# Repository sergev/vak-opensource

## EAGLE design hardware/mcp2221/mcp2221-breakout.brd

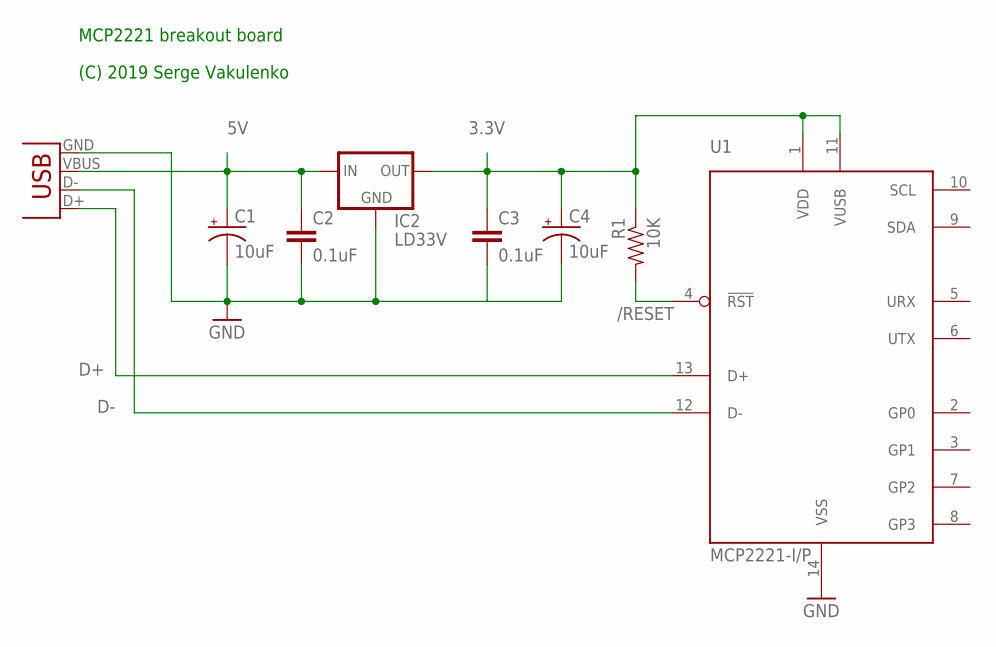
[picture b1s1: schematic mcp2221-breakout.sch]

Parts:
C1, C4: 10uF; CPOL-RADIAL-10UF-25V
C2: 0.1uF; CAP-PTH-SMALL
C3: 0.1uF; CAP-PTH-5MM
IC2: LD33V; 78XXL
R1: 10K; AXIAL-0.3
U1: MCP2221-I/P; DIL14
X1: USBPTH; USB-B-PTH

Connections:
3.3V: C3.1, C4.1 (+), IC2.OUT, R1.P$1 (1), U1.1 (VDD), U1.11 (VUSB)
5V: C1.1 (+), C2.1, IC2.IN, X1.VBUS
/RESET: R1.P$2 (2), U1.4 (!RST)
D+: U1.13 (D+), X1.D+
D-: U1.12 (D-), X1.D-
GND: C1.2 (-), C2.2, C3.2, C4.2 (-), IC2.GND, U1.14 (VSS), X1.GND

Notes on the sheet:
MCP2221 breakout board
(C) 2019 Serge Vakulenko

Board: 2 copper layers, 8 parts (0 on the bottom side), 6 nets, no tracks yet.

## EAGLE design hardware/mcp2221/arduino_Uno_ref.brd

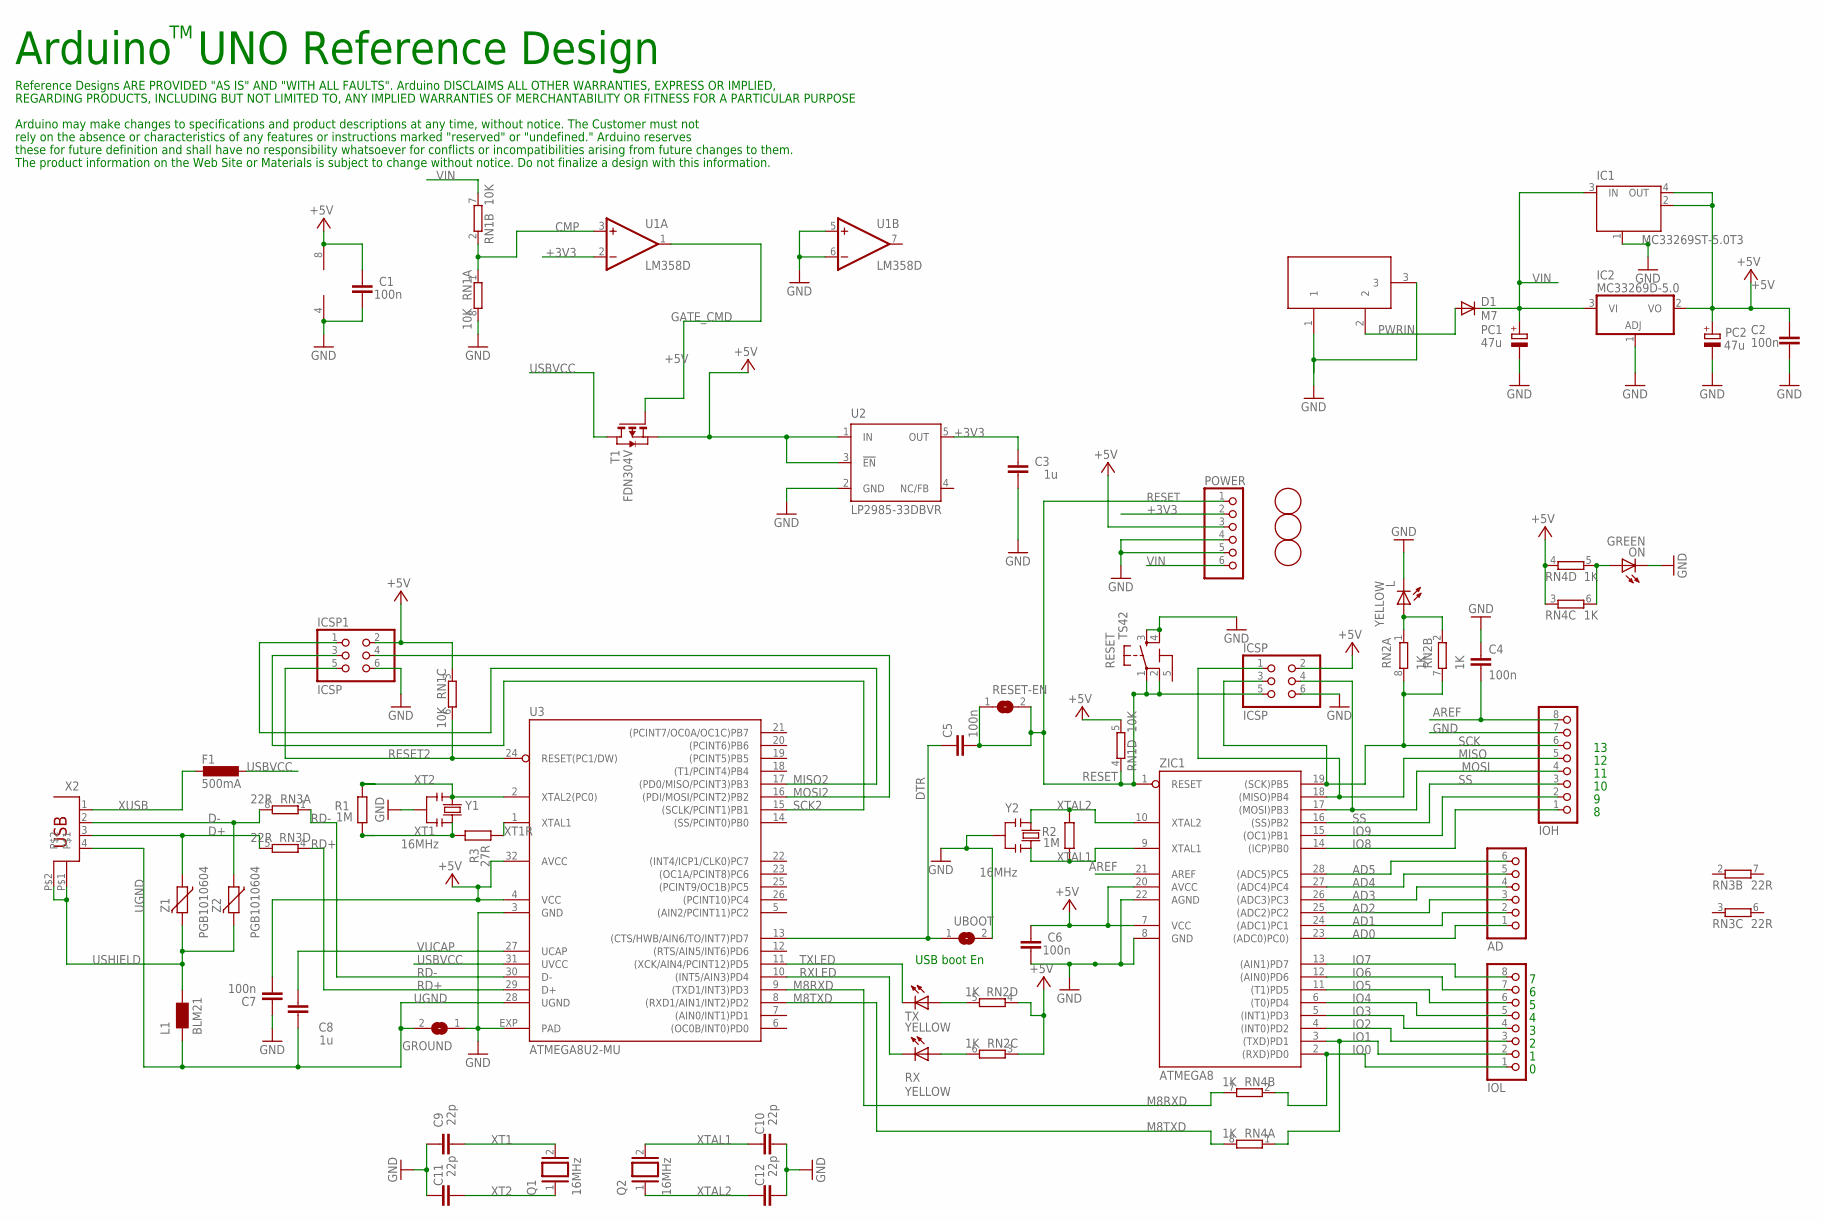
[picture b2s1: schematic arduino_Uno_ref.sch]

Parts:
AD: PINHD-1X6; 1X06
C1, C2, C4, C5, C6, C7: 100n; C0603-ROUND
C3, C8: 1u; C0603-ROUND
C9, C10, C11, C12: 22p; C0603-ROUND
D1: M7; SMB
F1: 500mA; L1812
GROUND: SJ
IC1: MC33269ST-5.0T3; SOT223
IC2: MC33269D-5.0; DPACK
ICSP, ICSP1: ICSP; 2X03
IOH: PINHD-1X8; 1X08
IOL: PINHD-1X8; 1X08
L: YELLOW; CHIP-LED0805
L1: BLM21; 0805
ON: GREEN; CHIP-LED0805
PC1, PC2: 47u; PANASONIC_D
POWER: PINHD-1X6; 1X06
Q1, Q2: 16MHz; QS
R1, R2: 1M; R0603-ROUND
R3: 27R; R0603-ROUND
RESET: TS42
RESET-EN: SJ
RN1: 10K; CAY16
RN2, RN4: 1K; CAY16
RN3: 22R; CAY16
RX: YELLOW; CHIP-LED0805
T1: FDN304V; SOT-23
TX: YELLOW; CHIP-LED0805
U1: LM358D; SO08
U2: LP2985-33DBVR; SOT23-DBV
U3: ATMEGA8U2-MU; QFN32
U$3, U$4, U$6: FIDUCIALMOUNT; FIDUCIA-MOUNT
UBOOT: SJ
X1: DC21MMX; DC-21MM
X2: PN61729
Y1, Y2: 16MHz; RESONATOR
Z1, Z2: PGB1010604; CT/CN0603
ZIC1: ATMEGA8; DIL28-3

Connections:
5-GND: RESET.5 (5-GND)
+3V3: C3.2, POWER.2, U1.2 (-IN), U2.5 (OUT)
+5V: C1.2, C2.2, C6.2, C7.1, IC1.2 (OUT), IC1.4 (OUT), IC2.2 (VO), ICSP.2, ICSP1.2, PC2.+, POWER.3, RN1.3 (1), RN1.5 (2), RN2.3 (1), RN2.4 (1), RN4.3 (1), RN4.4 (1), T1.2 (S), U1.8 (V+), U2.1 (IN), U2.3 (!EN), U3.4 (VCC), U3.32 (AVCC), ZIC1.7 (VCC), ZIC1.20 (AVCC)
AD0: AD.1, ZIC1.23 ((ADC0)PC0))
AD1: AD.2, ZIC1.24 ((ADC1)PC1)
AD2: AD.3, ZIC1.25 ((ADC2)PC2)
AD3: AD.4, ZIC1.26 ((ADC3)PC3)
AD4: AD.5, ZIC1.27 ((ADC4)PC4)
AD5: AD.6, ZIC1.28 ((ADC5)PC5)
AREF: C4.2, IOH.8, ZIC1.21 (AREF)
CMP: RN1.1, RN1.2 (1), U1.3 (+IN)
D+: RN3.5 (2), X2.3, Z1.1
D-: RN3.8 (2), X2.2, Z2.1
DTR: C5.1, U3.13 ((CTS/HWB/AIN6/TO/INT7)PD7), UBOOT.1
GATE_CMD: T1.3 (G), U1.1 (OUT)
GND: C1.1, C2.1, C3.1, C4.1, C6.1, C7.2, C9.2, C10.1, C11.2, C12.1, GROUND.1, IC1.1 (GND/ADJ), IC2.1 (ADJ), ICSP.6, ICSP1.6, IOH.7, L.C, ON.C, PC1.-, PC2.-, POWER.4, POWER.5, RESET.3, RESET.4, RN1.8 (2), U1.4 (V-), U1.5 (+IN), U1.6 (-IN), U2.2 (GND), U3.3 (GND), U3.EXP (PAD), UBOOT.2, X1.1, X1.3, Y1.2, Y2.2, ZIC1.8 (GND), ZIC1.22 (AGND)
IO0: IOL.1, RN4.2 (1), ZIC1.2 ((RXD)PD0)
IO1: IOL.2, RN4.1, ZIC1.3 ((TXD)PD1)
IO2: IOL.3, ZIC1.4 ((INT0)PD2)
IO3: IOL.4, ZIC1.5 ((INT1)PD3)
IO4: IOL.5, ZIC1.6 ((T0)PD4)
IO5: IOL.6, ZIC1.11 ((T1)PD5)
IO6: IOL.7, ZIC1.12 ((AIN0)PD6)
IO7: IOL.8, ZIC1.13 ((AIN1)PD7)
IO8: IOH.1, ZIC1.14 ((ICP)PB0)
IO9: IOH.2, ZIC1.15 ((OC1)PB1)
M8RXD: RN4.7 (2), U3.9 ((TXD1/INT3)PD3)
M8TXD: RN4.8 (2), U3.8 ((RXD1/AIN1/INT2)PD2)
MISO: ICSP.1, IOH.5, ZIC1.18 ((MISO)PB4)
MISO2: ICSP1.1, U3.17 ((PD0/MISO/PCINT3)PB3)
MOSI: ICSP.4, IOH.4, ZIC1.17 ((MOSI)PB3)
MOSI2: ICSP1.4, U3.16 ((PDI/MOSI/PCINT2)PB2)
unnamed: L.A, RN2.1, RN2.2 (1)
unnamed: ON.A, RN4.5 (2), RN4.6 (2)
unnamed: RN2.6 (2), RX.A
unnamed: RN2.5 (2), TX.A
PWRIN: D1.A, X1.2
RD+: RN3.4 (1), U3.29 (D+)
RD-: RN3.1, U3.30 (D-)
RESET: C5.2, ICSP.5, POWER.1, RESET.1, RESET.2, RESET-EN.1, RESET-EN.2, RN1.4 (1), ZIC1.1 (RESET)
RESET2: ICSP1.5, RN1.6 (2), U3.24 (RESET(PC1/DW))
RXLED: RX.C, U3.10 ((INT5/AIN3)PD4)
SCK: ICSP.3, IOH.6, RN2.7 (2), RN2.8 (2), ZIC1.19 ((SCK)PB5)
SCK2: ICSP1.3, U3.15 ((SCLK/PCINT1)PB1)
SS: IOH.3, ZIC1.16 ((SS)PB2)
TXLED: TX.C, U3.11 ((XCK/AIN4/PCINT12)PD5)
UGND: C8.2, GROUND.2, L1.1, U3.28 (UGND), X2.4
USBVCC: F1.1, T1.1 (D), U3.31 (UVCC)
USHIELD: L1.2, X2.P$1, X2.P$2, Z1.2, Z2.2
VIN: D1.C, IC1.3 (IN), IC2.3 (VI), PC1.+, POWER.6, RN1.7 (2)
VUCAP: C8.1, U3.27 (UCAP)
XT1: C9.1, Q1.2, R1.1, R3.2, Y1.3
XT1R: R3.1, U3.1 (XTAL1)
XT2: C11.1, Q1.1, R1.2, U3.2 (XTAL2(PC0)), Y1.1
XTAL1: C10.2, Q2.2, R2.1, Y2.3, ZIC1.9 (XTAL1)
XTAL2: C12.2, Q2.1, R2.2, Y2.1, ZIC1.10 (XTAL2)
XUSB: F1.2, X2.1

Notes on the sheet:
Arduino UNO Reference Design
USB boot En
Reference Designs ARE PROVIDED "AS IS" AND "WITH ALL FAULTS". Arduino DISCLAIMS ALL OTHER WARRANTIES, EXPRESS OR IMPLIED,
Arduino may make changes to specifications and product descriptions at any time, without notice. The Customer must not
REGARDING PRODUCTS, INCLUDING BUT NOT LIMITED TO, ANY IMPLIED WARRANTIES OF MERCHANTABILITY OR FITNESS FOR A PARTICULAR PURPOSE
rely on the absence or characteristics of any features or instructions marked "reserved" or "undefined." Arduino reserves
these for future definition and shall have no responsibility whatsoever for conflicts or incompatibilities arising from future changes to them.
The product information on the Web Site or Materials is subject to change without notice. Do not finalize a design with this information.

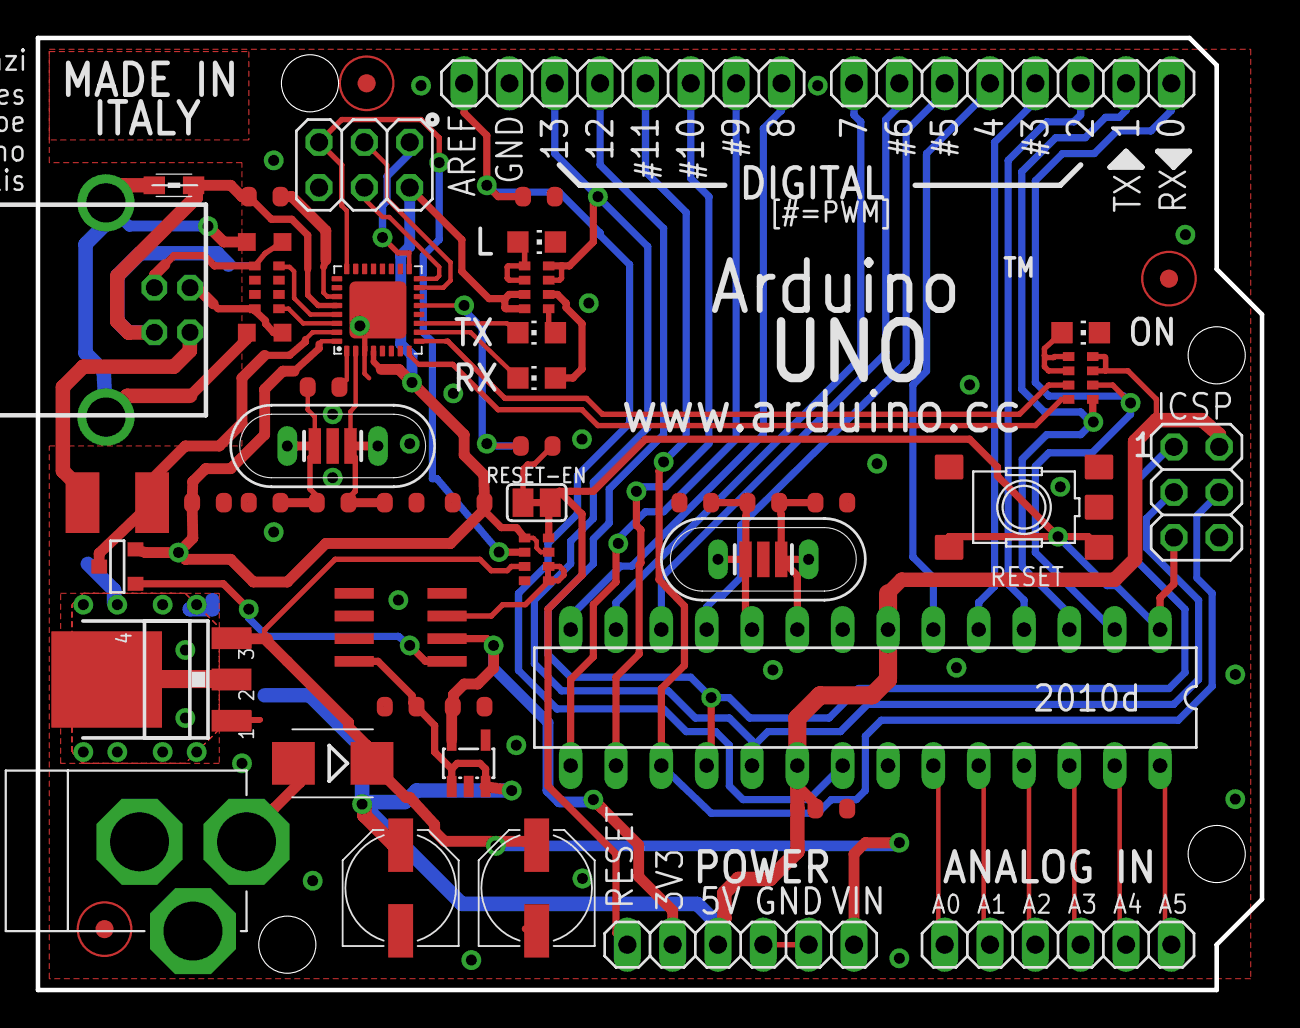
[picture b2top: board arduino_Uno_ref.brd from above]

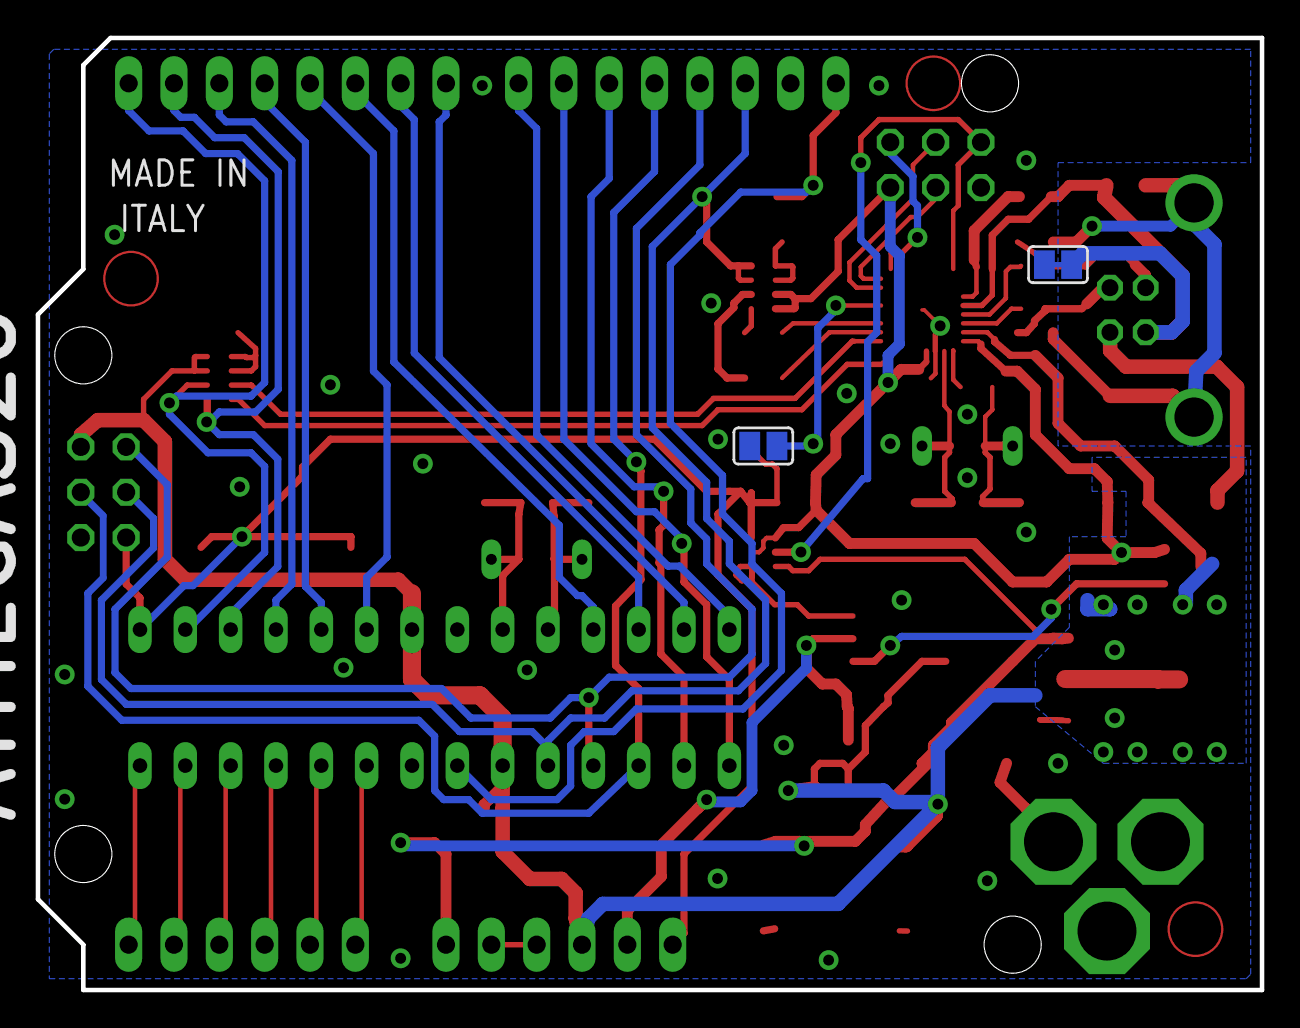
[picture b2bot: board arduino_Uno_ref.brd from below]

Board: 2 copper layers, 68.6 x 53.3 mm, 56 parts (2 on the bottom side), 56 nets.

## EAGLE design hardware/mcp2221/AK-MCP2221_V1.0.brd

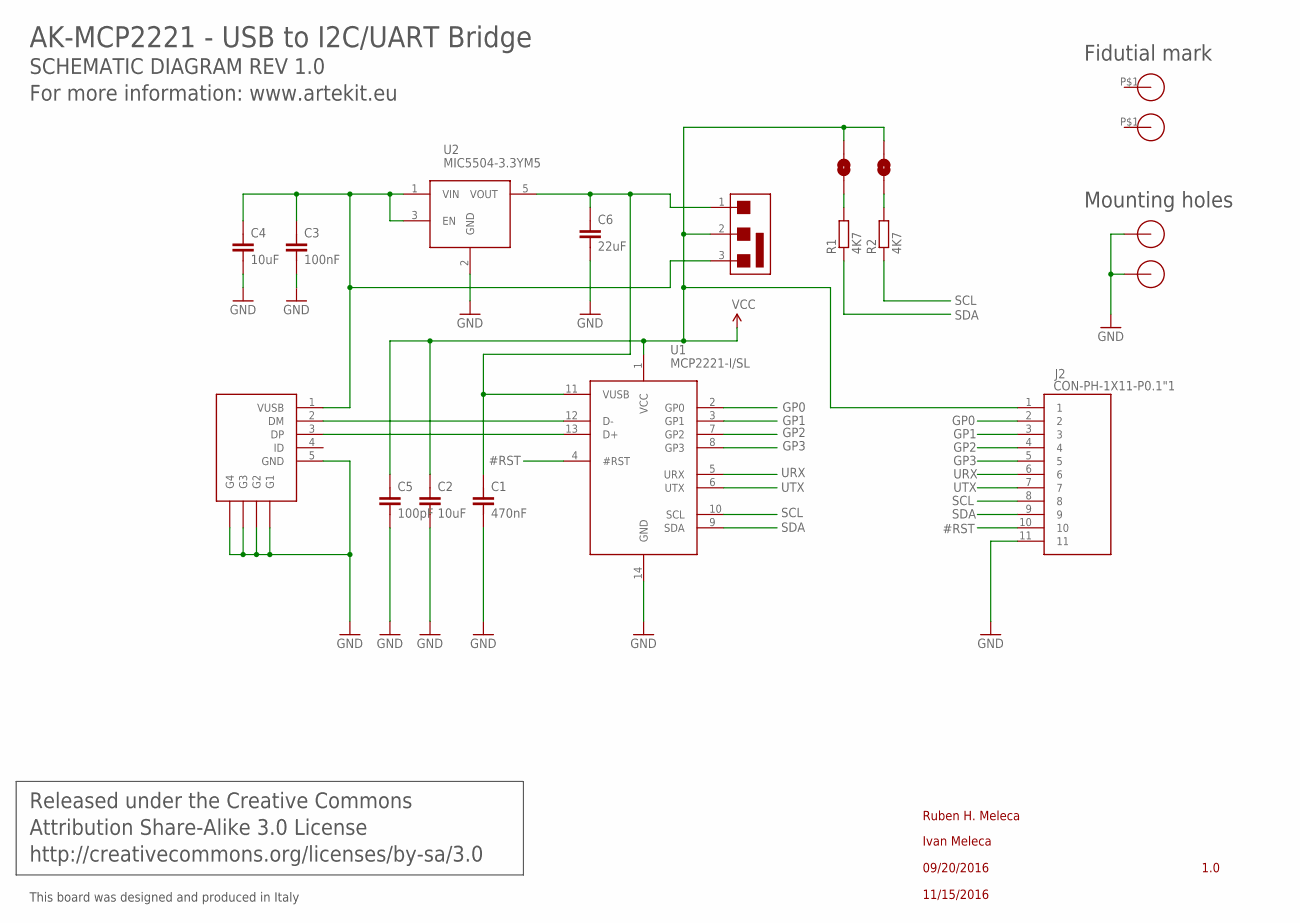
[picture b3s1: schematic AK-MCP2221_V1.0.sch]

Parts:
C1: 470nF; C0603
C2: 10uF; C0603
C3: 100nF; C0603
C4: 10uF; C0805
C5: 100pF; C0603
C6: 22uF; C0805
J1, J3: JUMPER-1-OPEN
J2: CON-PH-1X11-P0.1"1; PIN-HEADER-1X11
J4: CON-USB-MINI-B-SMD
R1, R2: 4K7; R0603
SW1: SSSS810701; SLIDE-SWITCH-3-WAY
U1: MCP2221-I/SL; SOICN-14
U2: MIC5504-3.3YM5; SOT23-5
U$2, U$3: HOLE-2MM-METALIZED
U$4, U$5: FIDUTIAL_1.2MM

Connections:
#RST: J2.10, U1.4 (#RST)
GND: C1.2, C2.2, C3.2, C4.2, C5.2, C6.2, J2.11, J4.5 (GND), J4.C (G1), J4.D (G2), J4.E (G3), J4.F (G4), U1.14 (GND), U2.2 (GND), U$2.1, U$3.1
GP0: J2.2, U1.2 (GP0)
GP1: J2.3, U1.3 (GP1)
GP2: J2.4, U1.7 (GP2)
GP3: J2.5, U1.8 (GP3)
unnamed: J4.2 (DM), U1.12 (D-)
unnamed: J4.3 (DP), U1.13 (D+)
unnamed: C3.1, C4.1, J4.1 (VUSB), SW1.3 (1), U2.1 (VIN), U2.3 (EN)
unnamed: C1.1, C6.1, SW1.1 (3), U1.11 (VUSB), U2.5 (VOUT)
unnamed: J1.1, R1.2
unnamed: J3.1, R2.2
SCL: J2.8, R2.1, U1.10 (SCL)
SDA: J2.9, R1.1, U1.9 (SDA)
URX: J2.6, U1.5 (URX)
UTX: J2.7, U1.6 (UTX)
VCC: C2.1, C5.1, J1.2, J2.1, J3.2, SW1.2, U1.1 (VCC)

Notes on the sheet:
Released under the Creative Commons
Attribution Share-Alike 3.0 License
http://creativecommons.org/licenses/by-sa/3.0
This board was designed and produced in Italy
Ruben H. Meleca
Ivan Meleca
09/20/2016
11/15/2016
1.0
AK-MCP2221 - USB to I2C/UART Bridge
SCHEMATIC DIAGRAM REV 1.0
For more information: www.artekit.eu
Mounting holes
Fidutial mark

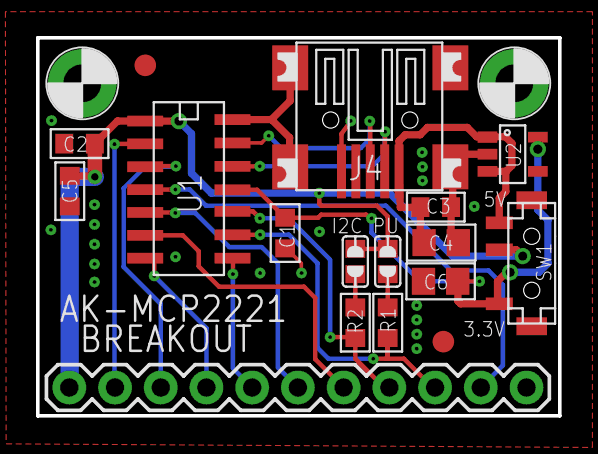
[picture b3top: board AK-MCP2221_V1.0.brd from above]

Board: 2 copper layers, 29.0 x 21.0 mm, 19 parts (0 on the bottom side), 17 nets.

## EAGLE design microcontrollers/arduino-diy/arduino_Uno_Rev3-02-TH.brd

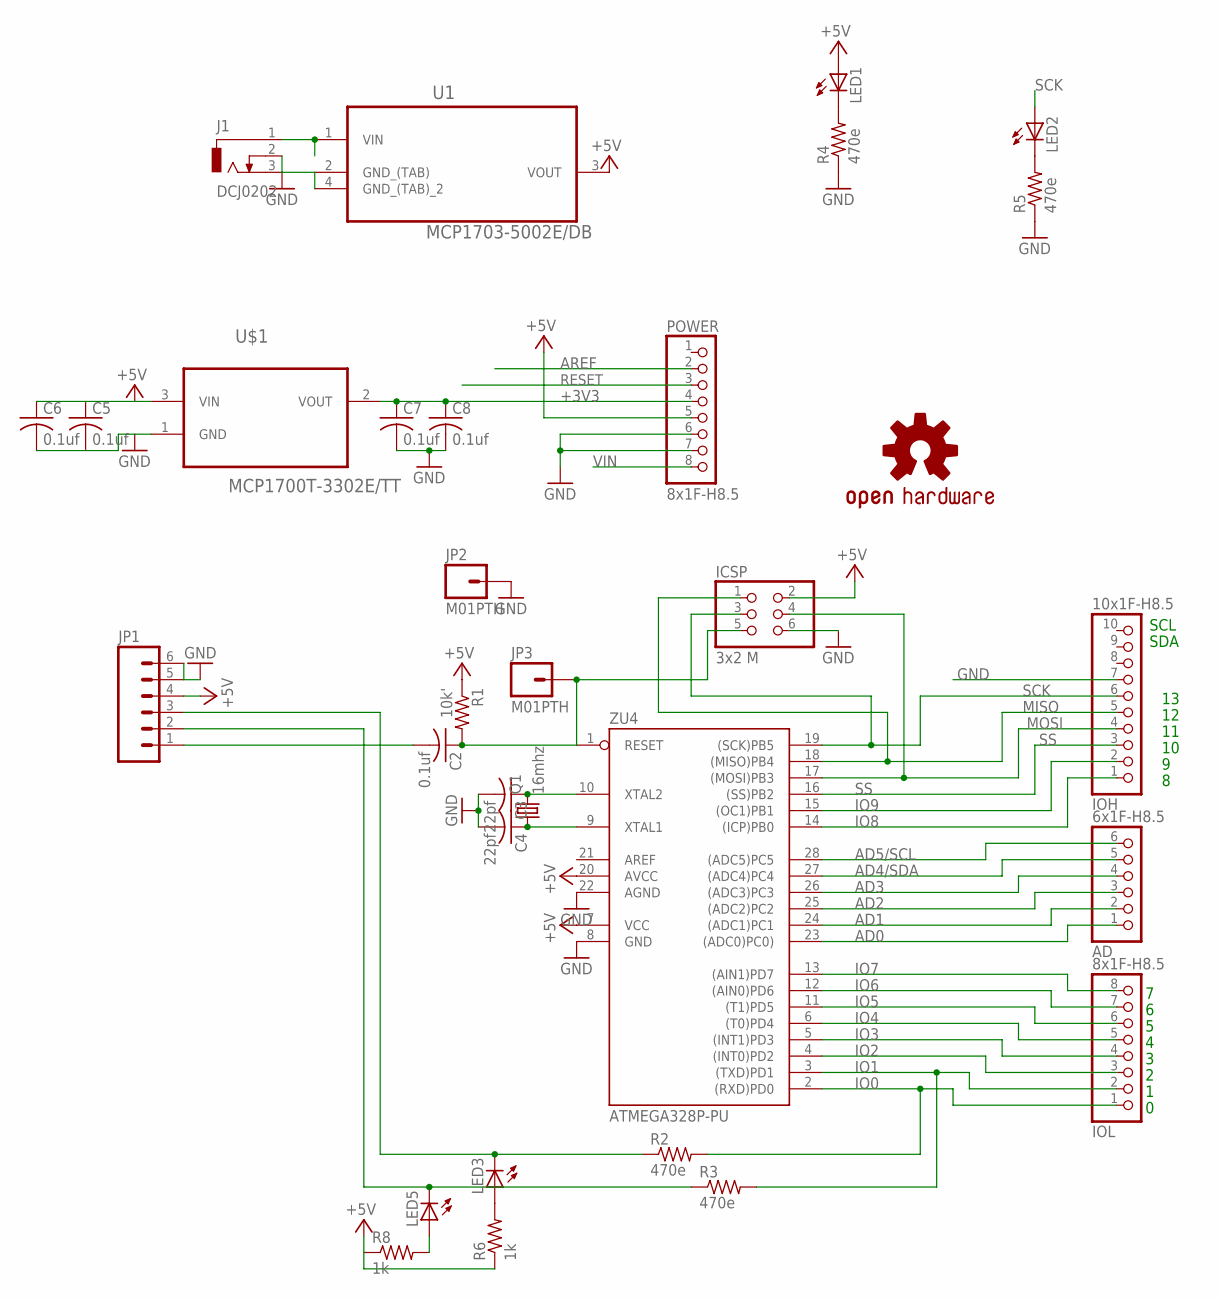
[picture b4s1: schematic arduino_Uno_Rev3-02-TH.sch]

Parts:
AD: 6x1F-H8.5; 1X06
C2, C5, C6, C7, C8: 0.1uf; C0603
C3, C4: 22pf; C1206
ICSP: 3x2 M; 2X03
IOH: 10x1F-H8.5; 1X10
IOL: 8x1F-H8.5; 1X08
J1: DCJ0202
JP1: M06LONGPADS; 1X06_LONGPADS
JP2, JP3: M01PTH; 1X01
LED1, LED2, LED3, LED5: LED3MM
LOGO1: OSHW-LOGOL; OSHW-LOGO-L
POWER: 8x1F-H8.5; 1X08
Q1: 16mhz; HC49/S
R1: 10k'; R0603
R2, R3, R4, R5: 470e; R0603
R6, R8: 1k; R0603
U1: MCP1703-5002E/DB; SOT230P700X180-4N
U$1: MCP1700T-3302E/TT; SOT95P237X112-3N
ZU4: ATMEGA328P-PU; DIL28-3

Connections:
+3V3: C7.1, C8.1, POWER.4, U$1.2 (VOUT)
+5V: C5.1, C6.1, ICSP.2, JP1.4, LED1.A, POWER.5, R1.1, R6.1, R8.1, U1.3 (VOUT), U$1.3 (VIN), ZU4.7 (VCC), ZU4.20 (AVCC)
AD0: AD.1, ZU4.23 ((ADC0)PC0))
AD1: AD.2, ZU4.24 ((ADC1)PC1)
AD2: AD.3, ZU4.25 ((ADC2)PC2)
AD3: AD.4, ZU4.26 ((ADC3)PC3)
AD4/SDA: AD.5, ZU4.27 ((ADC4)PC4)
AD5/SCL: AD.6, ZU4.28 ((ADC5)PC5)
AREF: POWER.2
GND: C3.2, C4.2, C5.2, C6.2, C7.2, C8.2, ICSP.6, IOH.7, J1.2, J1.3, JP1.5, JP1.6, JP2.1, POWER.6, POWER.7, R4.1, R5.1, U1.2 (GND_(TAB)), U1.4 (GND_(TAB)_2), U$1.1 (GND), ZU4.8 (GND), ZU4.22 (AGND)
IO0: IOL.1, R2.2, ZU4.2 ((RXD)PD0)
IO1: IOL.2, R3.2, ZU4.3 ((TXD)PD1)
IO2: IOL.3, ZU4.4 ((INT0)PD2)
IO3: IOL.4, ZU4.5 ((INT1)PD3)
IO4: IOL.5, ZU4.6 ((T0)PD4)
IO5: IOL.6, ZU4.11 ((T1)PD5)
IO6: IOL.7, ZU4.12 ((AIN0)PD6)
IO7: IOL.8, ZU4.13 ((AIN1)PD7)
IO8: IOH.1, ZU4.14 ((ICP)PB0)
IO9: IOH.2, ZU4.15 ((OC1)PB1)
MISO: ICSP.1, IOH.5, ZU4.18 ((MISO)PB4)
MOSI: ICSP.4, IOH.4, ZU4.17 ((MOSI)PB3)
unnamed: LED1.K (C), R4.2
unnamed: C3.1, Q1.2, ZU4.10 (XTAL2)
unnamed: C4.1, Q1.1, ZU4.9 (XTAL1)
unnamed: C2.2, JP1.1
unnamed: LED2.K (C), R5.2
unnamed: LED5.A, R8.2
unnamed: LED3.A, R6.2
RESET: C2.1, ICSP.5, JP3.1, POWER.3, R1.2, ZU4.1 (RESET)
RX_: JP1.3, LED3.K (C), R2.1
SCK: ICSP.3, IOH.6, LED2.A, ZU4.19 ((SCK)PB5)
SS: IOH.3, ZU4.16 ((SS)PB2)
TX_: JP1.2, LED5.K (C), R3.1
VIN: J1.1, POWER.8, U1.1 (VIN)

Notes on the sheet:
SDA
SCL

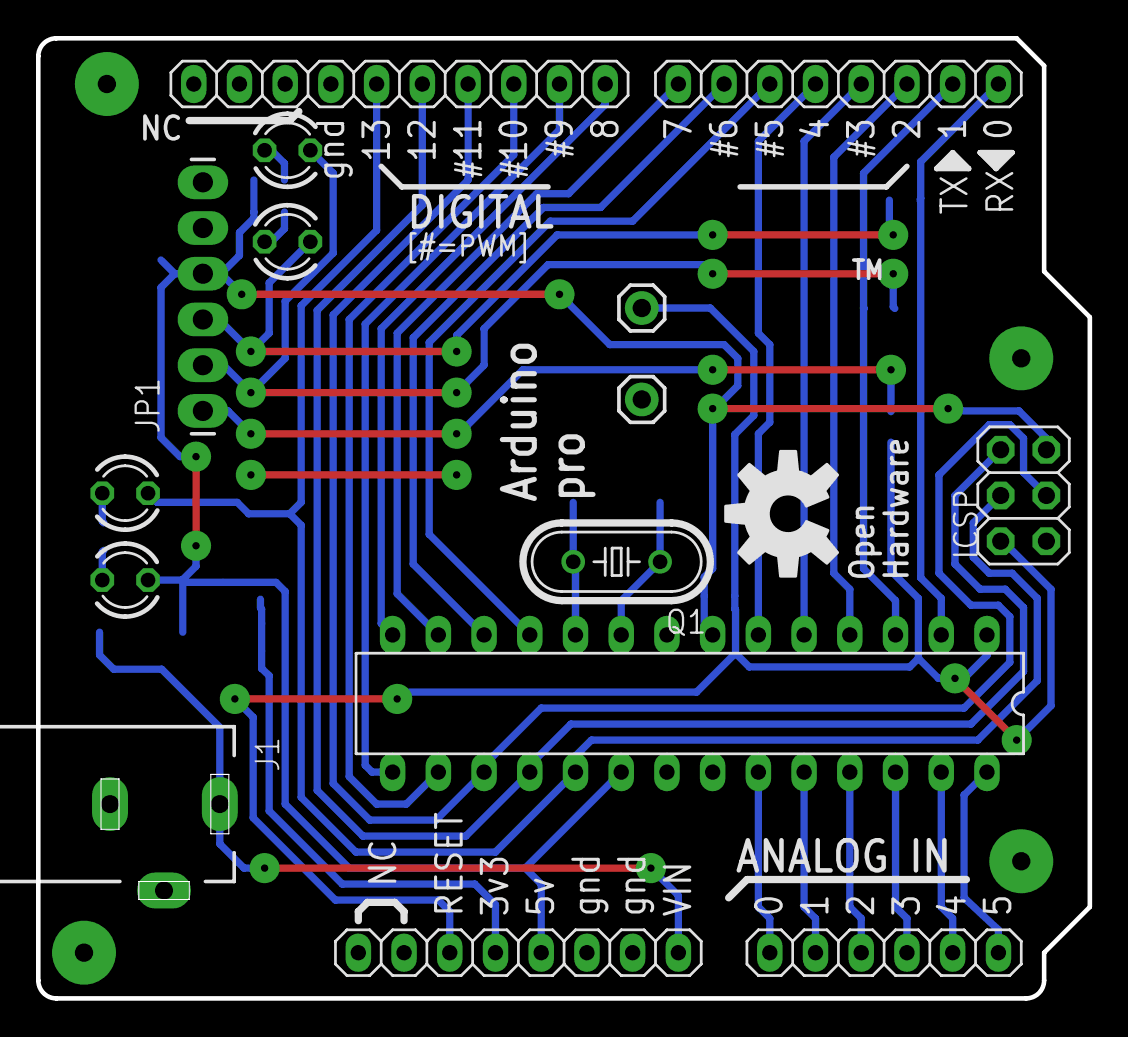
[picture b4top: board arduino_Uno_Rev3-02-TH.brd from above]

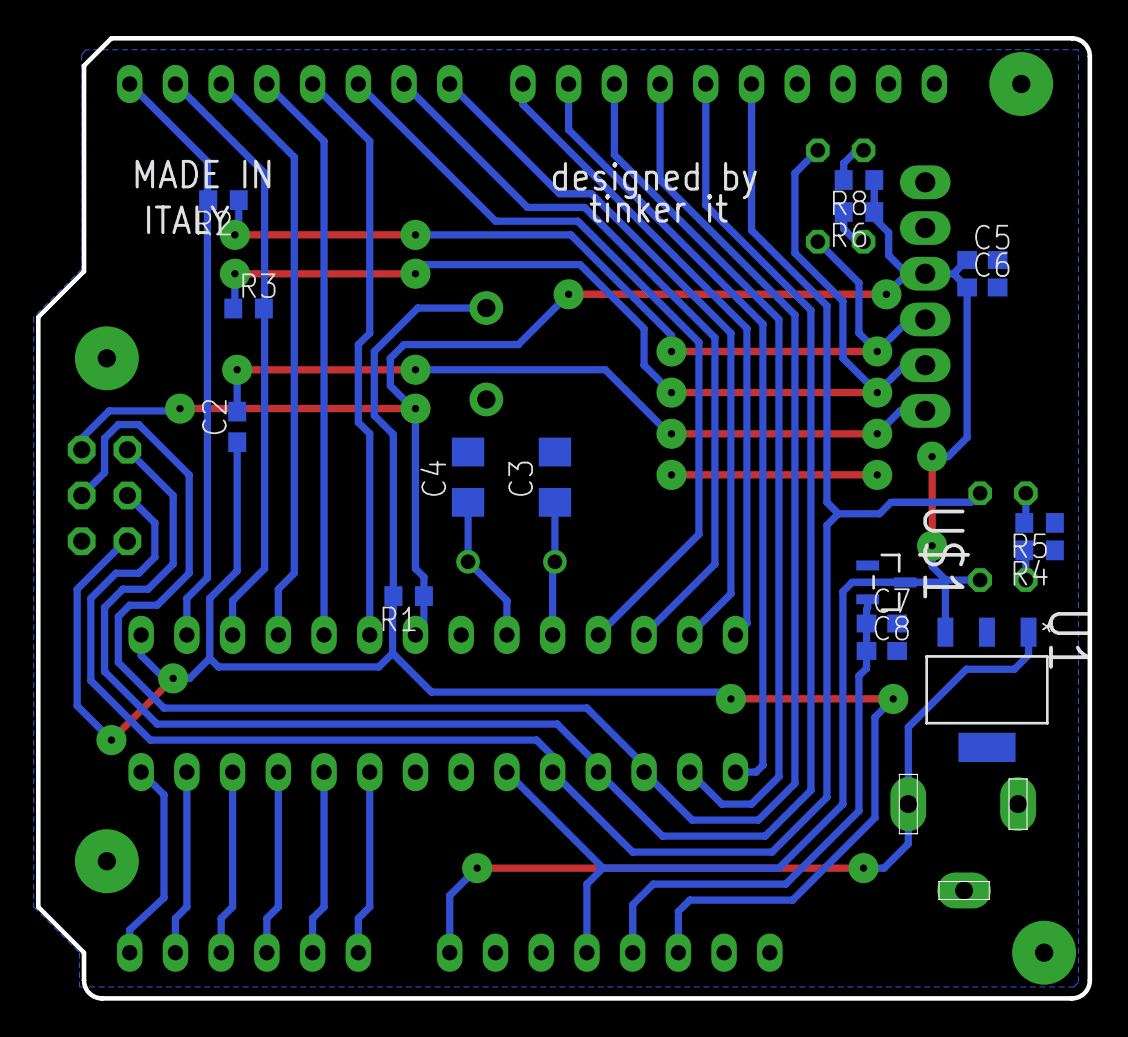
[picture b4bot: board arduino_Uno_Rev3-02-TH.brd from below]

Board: 2 copper layers, 58.4 x 53.3 mm, 32 parts (16 on the bottom side), 34 nets.

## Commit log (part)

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2024-01-27 Add demo of ARM SVE.
2024-01-27 Add demo of ARM Neon processor.
2024-02-06 Add 'sizes' program.
2024-02-06 Also print size of pointer and of size_t.
2024-02-08 Add float-limits.c.
2024-02-08 Implement ldouble.
2024-02-18 Fix onnx tool.
2024-02-18 Move onnx inspect demo.
2024-02-18 Create ONNX demo for restyling images.
2024-02-18 Update style for clang-format.
2024-02-18 Update onnx-restyle.
2024-02-18 Add copyright to onnx-restyle.
2024-02-23 New python demo: draw randomized pattern for a rug.
2024-02-24 Rug: optimize layout.
2024-02-24 Rug2: set corners to background color.
2024-03-02 Create example of matmul in C using SSE instructions.
2024-03-03 Matmul: add disassembly of Neon code.
2024-03-03 Simplify makefile.
2024-03-03 Rename matmul files.
2024-03-03 Update matmul sources.
2024-03-31 Add demo of Turbo Vision.
2024-03-31 Add Life demo for Turbo Vision.
2024-04-25 Add implementation of piece table in C from Red.
2024-04-29 Add skeleton for file segments implementation in C++.
2024-04-30 Isolate editor from curses.
2024-05-03 Add example in SETL: Eulerian path in a graph.
2024-05-04 Finish SETL example of Turing machine.
2024-05-04 Turing machine: restore the original view.
2024-05-05 Update Anchorhead script.
2024-05-05 Anchorhead: finish day 3.
2024-05-06 Anchorhead: clean up the walkthrough.
2024-05-06 Add files for game Cragne Manor.
2024-05-06 Add astronomy examples in C.
2024-05-08 Cragne Manor: finish levels 1-10.
2024-05-08 Update Cragne Manor script B.
2024-05-10 Cragne Manor: finish Town square.
2024-05-10 Cragne Manor: back to the Old Well.
2024-05-14 Cragne Manor: finish The Old Well.
2024-05-14 Finish Circular Room.
2024-05-14 Finish Constabulary Road.
2024-06-23 Add C++ example of recursive list.
2024-06-28 Translate four paragraphs of al-Khwarizmi.
2024-06-29 Update algoritmi.
2024-06-29 Translate algoritmi to English.
2024-06-29 Change difference -> place.
2024-07-12 Add sources of f77split.
2024-07-12 Make f77split work for besm6 sources.
2024-07-22 Add sources of Eliza in C++.
2024-07-28 Add sources of ALgol compiler for machines Electrologica X1 and X8.
2024-08-18 Add sources of sorting in Fortran.
2024-08-20 Add D example: man or boy.
2024-08-28 Modify Algol 60 examples for marst compiler.
2024-08-28 Add Algol60 example: JAZ164, R743, Outer Planets.
2024-08-31 Create game 'bulls and cows' in C.
2024-08-31 Add example of 'bulls and cows' in Algol 60.
2024-09-10 Add lisp sources in Algol-60.
2024-09-14 Fix lisp.
2024-09-20 Update esp-idf examples.
2024-09-20 Add example of Swift application build with CMake.
2024-10-08 Convert to utf8.
2024-10-09 Modify to compile with c99.
2024-10-09 Enable all warnings.
2024-10-10 Fix gcc issues.
2024-10-24 Add examples of unlimited precision integers in C++ using GMP++ library.
2024-10-24 Update Python examples.
2024-10-25 Enhance N-times demo.
2024-11-07 Add logs from PIC64GX Curiosity board.
2024-11-07 Add lscpu.txt for pic64.
2024-11-08 More assembly examples for RISC-V.
2024-11-08 Create assembly routine print_string.
2024-11-08 Simplify RISC-V assembly demos.
2024-11-10 Add C examples of cubic root and of Kahan sequence.
2024-11-10 Simplify cubic root.
2024-11-10 Create factorial example with printf.
2024-11-12 Create assembly files for overflow demo for amd64 architecture.
2024-11-12 Create assembly files for overflow demo for arm64 architecture.
2024-11-17 Add utility to print decimal floating point values.
2024-11-17 Fix decimal FP arithmetics.
2024-11-27 Add fibonacci example for Swift.
2024-12-03 Add boot log for Olimex A20-OLinuXino-LIME2 board.
2024-12-03 Update assembly 'hello world' examples for arm32 architecture.
2024-12-04 Add demo of Lorenz attractor in C.
2024-12-04 Update Lorenz demos.
2024-12-08 Add gitignore script.
2024-12-09 Print resident memory correctly on Linux.
2024-12-09 Use types of fixed size.
2024-12-09 Create script to run set/map benchmarks.
2024-12-09 Add results for Intel iMac.
2024-12-09 Update results for Apple M2.
2024-12-09 Update results for Intel iMac.
2024-12-09 Add results for Raspberry Pi 4 (FreeBSD).
2024-12-09 Add boot log of FreeBSD on Raspberry Pi 4.
2024-12-09 Cleanup.
2024-12-09 Add set/map results for Apple M1.
2024-12-10 Add set/map results for virtual Ubuntu on Apple M2 Max.
2024-12-10 Add configuration of Mac Mini M1.
2024-12-10 Add set/map results for virtual Chimera Linux on Apple M2 Max.
2024-12-10 Add set/map results for virtual MacOS on Apple M2 Max.
2024-12-14 Create initial version of cputrace for MacOS.
2024-12-14 Try to use PT_GETREGS.
2024-12-14 Port to Linux.
2024-12-14 Disassemble instructions.
2024-12-14 Rename to bintrace.
2024-12-14 Bintrace moved to github.com/sergev/bintrace.
2024-12-16 Add demo of a dynamic library on FreeBSD with arm32 processor.
2024-12-16 Add readme.
2024-12-16 Add assembly demo of a dynamic library on FreeBSD with arm32 processor.
2024-12-18 Add demo of a dynamic library linked at run time, on MacOS with arm64 processor.
2024-12-19 Add file foobar.bintrace.
2024-12-20 Remove flag -fPIE.
2024-12-21 Add assembly example for mips32.
2024-12-25 Add 'hello meson' example.
2024-12-25 Update readme.
2024-12-27 Move game-of-go to a separate repo.
2025-01-15 Enhance the gpio menu.
2025-01-15 Add signals GPIO 23, 24, 25.
2025-01-21 Add examples in Algol-68.
2025-02-07 Fix pic32 meb2 uart example. Add files for raspberry-pico lcd demo.
2025-02-08 Create script to run pic32-max32 demo on QEMU.
2025-02-12 Add games/tetris/.gitignore to ignore executable
2025-02-13 Add build_and_run.sh; uart.c: improve code logic
2025-02-13 Add README.md
2025-02-15 Add info about iBook G4.
2025-02-18 Update clock.c, from savchyn. See PR #1.
2025-02-21 Add gjs examples.
2025-02-22 Fix makefile for mozjs demo.
2025-02-26 Add editor in Rust. Add Box<T> implementation in C++.
2025-02-27 Add Rust's Result<T, E> implemented in C++.
2025-02-28 Add Rust's Arc<T> re-implemented in C++.
2025-02-28 Add Rust's Weak for Rc implementation in C++.
2025-02-28 Add Weak for Arc implementation in C++.
2025-02-28 Add Option implementation in C++.
2025-03-02 Update cell.cpp.
2025-03-02 Add C++ implementations of Rust's Mutex, RwLock and Cow.
2025-03-07 Add demos for Dear PiGui and PySide6.
2025-03-07 Add Rust examples of egui and native dialogs.
2025-03-30 Add C11 grammar files from: https://www.quut.com/c/ANSI-C-grammar-l-2011.html https://www.quut.com/c/ANSI-C-grammar-y-2011.html
2025-03-30 Add ASDL defininion of Python syntax.
2025-04-01 Add examples of parsers for arithmetic expressions and for simplified C language, based on ungrammar spec. Code was generated by grok.com.
2025-04-01 Add readme for C parser.
2025-04-06 Add parser for B in Rust.
2025-04-06 Add examples in Modula-2.
2025-04-28 Simplify.
2025-04-28 Encode UTF-16 properly.
2025-05-01 Add a skeleton of terminal emulator.
2025-05-01 Build term on MacOS.
2025-05-01 Unmap CR to NL on input.
2025-05-01 Use SDL library.
2025-05-01 Implement double buffering.
2025-05-01 Parse ANSI escape sequences.
2025-05-01 Add blinking cursor.
2025-05-01 Implement per-character colors.
2025-05-01 Process Esc c sequence, with debug.
2025-05-01 Fix bug in Esc-[-K.
2025-05-02 Add sources of SDL2 keycode finder.
2025-05-05 Create a demo for ncurses, which prints input keycodes.
2025-05-09 Another version of preprocessor, from grok.com.
2025-05-09 Add scanner of C grammar with tests, generated by grok.
2025-05-10 Implement character literals. Implement string and character prefixes L, u, U, u8.
2025-05-10 Use TOKEN_ prefix.
2025-05-10 Fix hex literals.
2025-05-10 Add comments for token types.
2025-05-10 Add ASDL definition of C grammar, from grok.
2025-05-10 Add sources of C parser from grok.
2025-05-13 Add shell script to print extended ASCII.
2025-05-15 Create script to print Latin Extended block.
2025-05-15 More scripts to print Unicode blocks.
2025-05-19 Re-indent.
2025-05-19 Store key inside node.
2025-05-19 Enhance remove_node(), avoid strcpy.
2025-05-19 Implement map_remove_cond().
2025-05-19 Add MIT license.
2025-06-02 Implement /bin/echo in OCaml.
2025-06-02 Enhance goecho.go.
2025-06-03 Create Turing machine which adds two numbers.
2025-06-05 Add Turing machine in C++.
2025-06-05 Reimplement Turing machine using std::deque.
2025-06-10 Implement minimizer of Boolean functions, in Python and in Rust. The code uses the Quine-McCluskey algorithm.
2025-06-10 Enhanced version of boolean minimizer.
2025-06-11 Get rid of BitVec.
2025-06-11 Fix bug in into_par_iter().
2025-06-11 Update tests.
2025-06-11 Fix issues in tests.
2025-06-11 First version of logic minimizer in C++.
2025-06-11 Compile the logic minimizer.
2025-06-11 Re-implement minimizer.
2025-06-11 Create logic minimizer in C.
2025-06-11 Create unit tests for can_merge().
2025-06-11 Split can_merge() into a separate file.
2025-06-11 Restore previous version of C++ minimizer. Fix three-variable test.
2025-06-11 Decrease thread level.
2025-06-11 Fix Python minimizer.
2025-06-11 Rust minimizer: print variables correctly. Update tests.
2025-07-10 Add progress bar in philosophers.
2025-07-10 Enable colors in philosophers.
2025-07-11 Add SortUI.app written in Swift.
2025-07-13 Add script for Russian->Latin encoding.
2025-07-15 Update script for Russian->Latin encoding.
2025-08-20 Ask Grok from Python script.
2025-08-21 Create script: retrieve a list of all human protein records from UniProt/SwissProt.
2025-08-21 Retrieve protein sequence and cross-references from UniProt for a given accession.
2025-08-22 Rename.
2025-08-25 Add script to fetch a list of all circovirus proteins.
2025-08-28 Add Python scripts for IP-XACT.
2025-09-23 Add two examples of C++ only projects built using SwiftPM.
2025-09-23 Implement library in C++ and tests in Swift.
2025-10-01 Add example of article rendered using Pandoc to PDF and HTML.
2025-10-01 Add a Python script which converts Markdown into ODT document.
2025-10-03 Add sysinfo for Google phone Pixel 7 Pro.
2025-10-03 Add example of drawing Stern–Brocot tree using LaTeX.
2025-10-04 Extend Russian example for Pandoc.
2025-10-04 Remove tikz from examples.
2025-10-04 Enhance kozak.svg.
2025-10-04 Add example of vectorizing a color PNG image into SVG picture.
2025-10-06 Update dhrystones for Pixel phone.
2025-10-08 Add Algol 60 syntax definition for CotEditor.
2025-10-10 Use io::treadline().
2025-10-10 Use os::exit().
2025-10-10 Get rid of strtoul().
2025-11-05 Enhance readme for cedit.
2025-11-07 Add example of async adder in Go.
2025-11-07 Add a benchmark of shared_ptr versus GC in C++.
2025-11-19 Implement unification in OCaml from scratch.
2025-11-26 Add a script which shows directory contents as a graph.
2025-12-01 Convert TCALC from the original Borland C++ 2.0 DOS implementation to use the ncurses library for Unix/Linux compatibility.
2025-12-09 Add scrlib library for DOS.
2025-12-11 Enhance rtclock.
2025-12-13 Add demo of metal-cpp.
2026-02-11 Fix unicoder.
2026-02-19 Implement reset recovery.
2026-02-19 Get floppy info via SG_IO.
2026-02-19 More experiments with USB format.
2026-02-19 Show floppy info via /dev/sg.
2026-02-19 Decode info pages.
2026-02-19 Create format utility.
2026-02-19 Add sources of floppy format.
2026-02-19 Fix -i option in format utility.
2026-02-23 Add C program and collected data about BIOS keyboard scancodes.
2026-04-08 Add sysinfo about Sun Netra 240 server.
2026-04-10 Add sysinfo from OpenBSD 7.8 on Sun Netra 240 server.
2026-04-11 Measure speed of Sun Netra 240 with dhrystone and duremark.
2026-04-11 Add neofetch for Sun Netra/OpenBSD.
2026-04-18 Add spigot-pi from https://litwr2.github.io/pi/pi-spigot-benchmark.html
2026-04-19 Add hello world in assembly for NASM on macOS x86-64.
2026-04-22 Find optimal strategy in Hamurabi game.
2026-04-22 Fix markdown link formatting in Strategy.md
2026-04-22 Implement optimal Hamurabi strategy in Python.
2026-04-22 Update the Python version of the Hamurabi bot.
2026-04-23 Enhance the Hamurabi strategy.
2026-04-28 Add duremark for MacBookPro11.2.

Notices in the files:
parts and their libraries:
SparkFun-Connectors: Licensing: Creative Commons ShareAlike 4.0 International - https://creativecommons.org/licenses/by-sa/4.0
